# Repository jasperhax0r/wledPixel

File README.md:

# wledPixel
ESP32 or ESP8266 and MAX7219 dot matrix display management

## Notes
1. Currently it does take some time for the initial setup to become ready, usually under a minute before you can connect to its SSID
2. After resetting to factory defaults you may have to powercycle.
3. WOPR mode doesnt really have any current settings, only thing that can be configured is what workzone its in and brightness.

[The latest firmware version can be found in Releases](https://github.com/jasperhax0r/wledPixel/releases)

## Supported key features:
1. **Home Assistant client** [display sensor values]
2. **OpenWeatherMap client** [display: temperature (C/F), humidity, pressure, wind speed, weather icon]
3. **MQTT client** [each display zone support own topic]
4. Display controll through MQTT
5. **Wall NTP clock** [NTP sync clock]
6. **WOPR Blinking Lights**
7. **Manual input**
8. Full controll through **web UI**
9. Home Assistant MQTT discovery [When MQTT settings specified, device will be automatically send discovery message to HA]
10. Control display as light in Home Assistant [MQTT setup required]
11. Initial setup through wifi AP and web UI
12. Support 3 independent display zones
13. Support up to 12 display segments at the same time [configured in web UI]
14. Included 3 different fonts
15. Plus symbols font

##### Ingredients:
1. Dot matrix display MAX7219, something like this: https://aliexpress.com/item/32618155357.html
2. ESP32 or WeMos D1 Mini (ESP8266), something like this: https://aliexpress.com/item/32651747570.html

## Web UI - Settings

##### Firmware compiled with next parameters:
**ESP32**
NOTE: I had problems with some ESP32 modules and couldnt get them to consistantly work or boot at all.
```
// Display pinout
#define DATA_PIN  23         // ESP32 GPIO23
#define CS_PIN    5          // ESP32 GPIO5
#define CLK_PIN   18         // ESP32 GPIO18

// Ds18b20 pinout
const int oneWireBus = 4;    // ESP32 GPIO04
```

**ESP8266**
```
// Display pinout
#define DATA_PIN  D7         // WeMos D1 mini or ESP8266 -> GPIO13
#define CS_PIN    D6         // WeMos D1 mini or ESP8266 -> GPIO12
#define CLK_PIN   D5         // WeMos D1 mini or ESP8266 -> GPIO14

// Ds18b20 pinout
const int oneWireBus = D4;   // WeMos D1 mini or ESP8266 -> GPIO02
```

## Wiring

Note: when I was removing the pins so that i could solder the modules together I ran into constant problems with the pads ripping off the matrix modules. most of the time the fix was easy as the 5v, ground, CS and CLK pins are all wired in parallel. however for the DIN that required soldering a jumper wire from the DIN pin on the header to one of the pins on the MAX7219 chip. not too hard but just wanted to note this,

Also as a work in progress I have made a full [12 module single board](https://github.com/jasperhax0r/wledPixel/FullSizePCB/) in KiCad for a more simpler install. However currently it is cost prohibitive in low quantities.

## First boot:
> - Device will boot in wifi access point mode and write the wifi name and password on the display.
> - AP wifi name: **wledPixel-[short MAC address]**
> - AP wifi password: **12345678**
> - Connect to this AP and configure your wifi settings (connect to your wifi network)
> - When the device connects to the WIFI network, the device's IP address will be displayed on the zone0
> - Open the browser and go to the device IP address

## API
```
/api/temperature      - get measured temperature from connected ds18b20 sensor
```

## Icons in Wled symbol font:

```
1 - "X"
2 - "stop"
3 - "rain"
4 - "ip:"
8 - "full light segment"
A - "calendar"
B - "windows"
C - "clouds"
D - "door"
E - "female"
F - "snowflake"
G - "key"
H - "male"
I - "alarm"
J - "clock"
K - "garbage"
L - "info"
M - "moon"
N - "message"
O - "reminder"
P - "wifi"
R - "huge rain"
S - "sun"
T - "thunderstorm"
c - "cloud"
f - "fog"
m - "cloud and moon"
r - "rain"
s - "sun and cloud"
° - "degree symbol"
```

## MQTT topics:
* `devicePrefix/zoneN/workMode`         - zone work mode
* `devicePrefix/zoneN/scrolleffectIn`   - scroll effect IN
* `devicePrefix/zoneN/scrolleffectOut`  - scroll effect Out
* `devicePrefix/zoneN/scrollspeed`      - scroll speed
* `devicePrefix/zoneN/scrollpause`      - scroll pause
* `devicePrefix/zoneN/scrollalign`      - scroll alignment
* `devicePrefix/zoneN/charspacing`      - character spacing
* `devicePrefix/intensity`              - brightness
* `devicePrefix/zoneN/workMode`         - zone work mode
* `devicePrefix/power`                  - display power control, support on / off values

where **devicePrefix** = wledPixel-A071
**zoneN** = zone number (e.g. Zone0)

#### Supported workMode:
workMode supported values:
* `mqttClient`    - MQTT client
* `manualInput`   - Manual static text inputed in UI
* `wallClock`     - NTP sync clock
* `owmWeather`    - Open Weather Map client
* `haClient`      - Home Assistant client
* `wopr`          - WOPR Blinking Lights Mode

## Wall clock
Wall clock mode support next following display options:
* `HH:MM`       - Hours : Minutes [21:43]
* `HH:MM:SS`    - Hours : Minutes : Seconds [21:43:54]
* `HH`          - Hours [21]
* `MM`          - Minutes [43]
* `dd.mm.yyyy`  - Day.Month.Year [21.06.2022]
* `dd.mm`       - Day.Month [21.06]
* `dd.mm aa`    - Day.Month weekday name (e.g., Sun) [21.06 Tue] *in Cyrillic font weekday name will be in Cyrillic
* `aa`          - Weekday name (e.g. Sun) *in Cyrillic font weekday name will be in Cyrillic

## Scroll effect list
Default effects:
* `PA_RANDOM`
* `PA_PRINT`
* `PA_SCAN_HORIZ`
* `PA_SCROLL_LEFT`
* `PA_WIPE`
* `PA_SCAN_VERTX`
* `PA_SCROLL_UP_LEFT`
* `PA_SCROLL_UP`
* `PA_FADE`
* `PA_OPENING_CURSOR`
* `PA_GROW_UP`
* `PA_SCROLL_UP_RIGHT`
* `PA_BLINDS`
* `PA_CLOSING`
* `PA_GROW_DOWN`
* `PA_SCAN_VERT`
* `PA_SCROLL_DOWN_LEFT`
* `PA_WIPE_CURSOR`
* `PA_SCAN_HORIZX`
* `PA_DISSOLVE`
* `PA_MESH`
* `PA_OPENING`
* `PA_CLOSING_CURSOR`
* `PA_SCROLL_DOWN_RIGHT`
* `PA_SCROLL_RIGHT`
* `PA_SLICE`
* `PA_SCROLL_DOWN`

## Home Assistant automation example:
Send sensor value each time when a value has been changed
```
---
- alias: Outside temp change - send new temp to wled panel mqtt
  initial_state: 'on'
  trigger:
    platform: state
    entity_id: sensor.outside_thp_sensor_3
  action:
    - service: mqtt.publish
      data:
        topic: wledPixel-A071/zone0/text
        payload_template: "{{ states('sensor.outside_thp_sensor_3') }} C"
```
Change **wledPixel-A071** to device name with your prefix

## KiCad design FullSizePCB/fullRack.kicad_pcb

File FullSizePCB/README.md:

# Full Size PCB Schematics and Gerber Files

## About the PCB
This PCB is basically 12 single modules connected together as one, using only through hole components to make it easier to hand solder.

*Note: while designed looking up the costs for the parts it is cheaper by far to just connect several premade modules together*

## BOM
* 12 x MAX7219CNG+
* 12 x 10k Resistors
* 12 x 0.1uF Ceramic Capacitors
* 12 x 10uF/25v Ceramic Capacitors
* 12 x TA08-81GWA 8x8 Matrix LED's
* 1 x 5pin Header

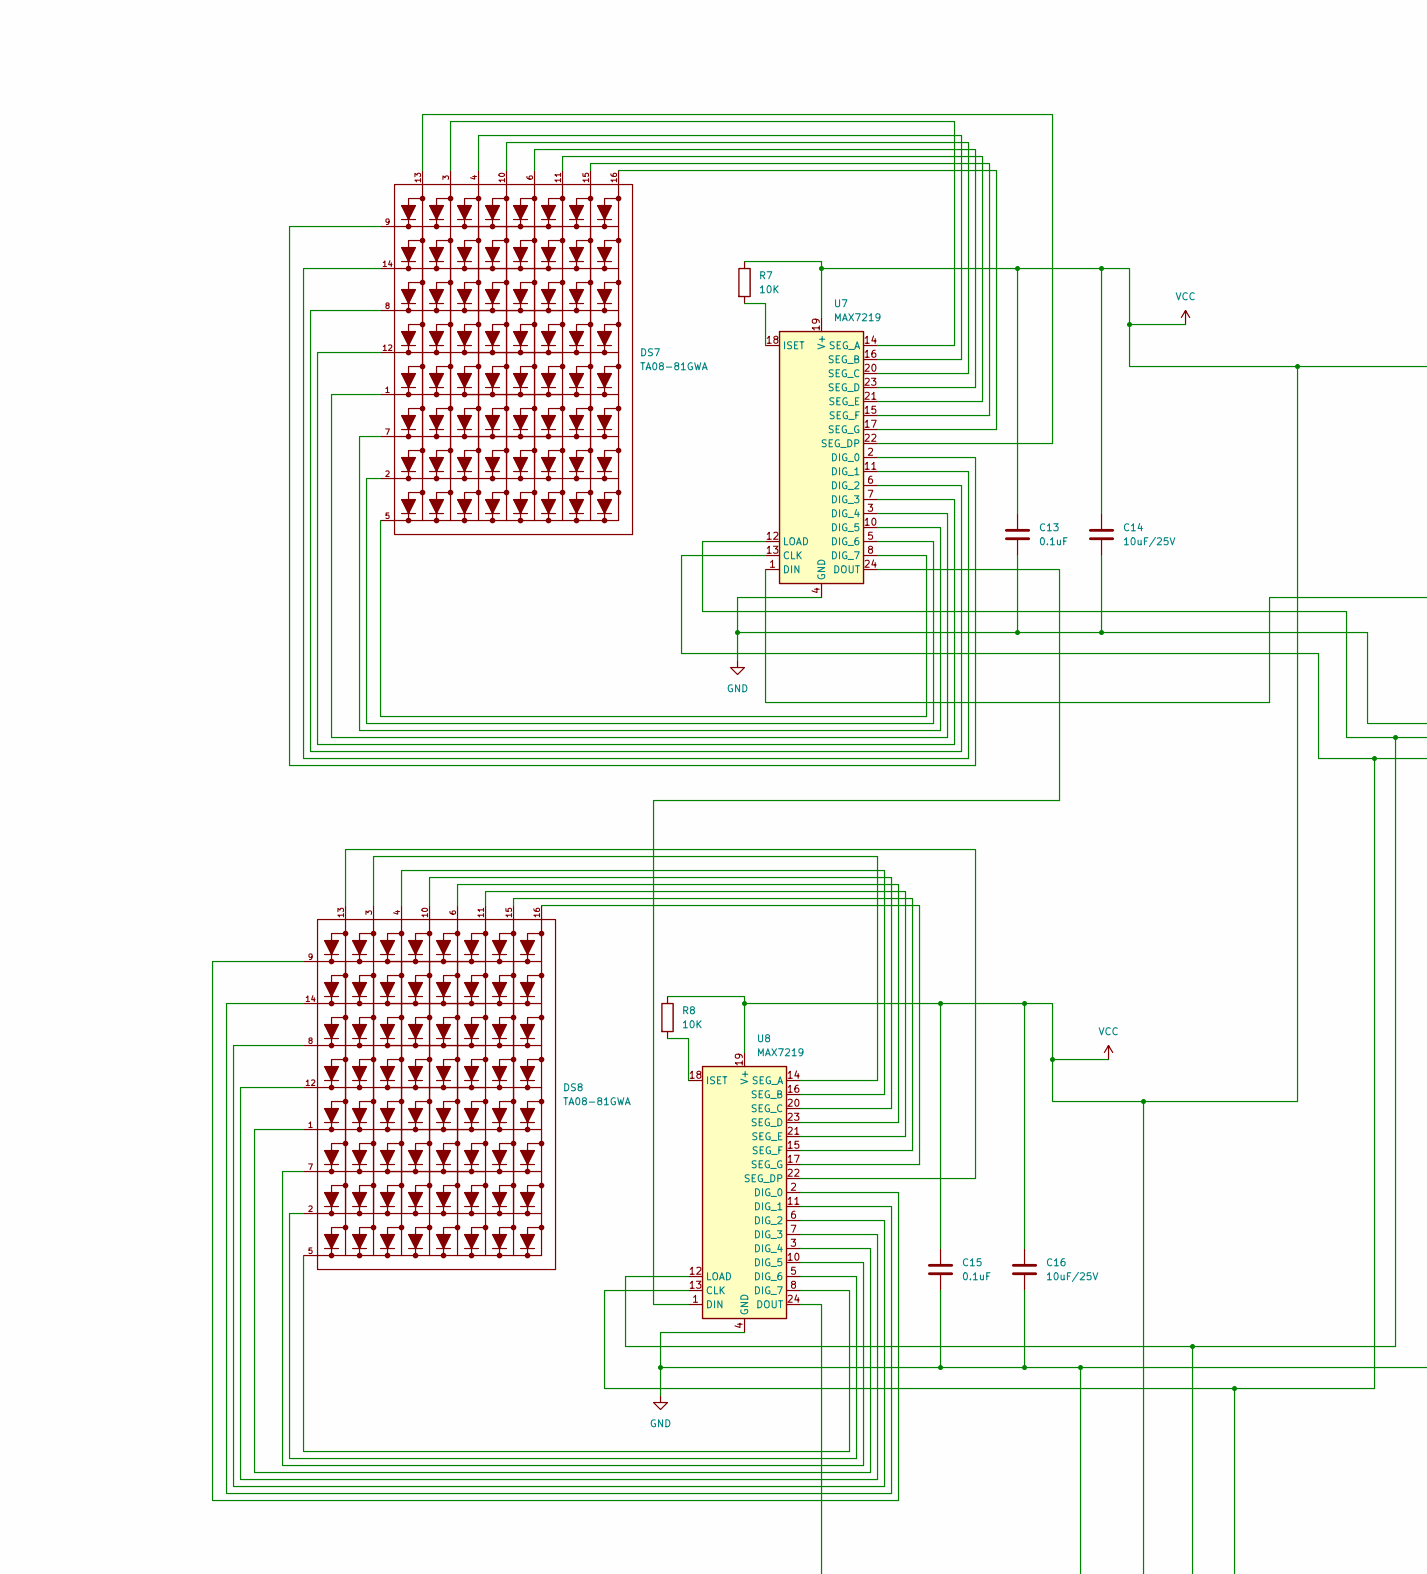
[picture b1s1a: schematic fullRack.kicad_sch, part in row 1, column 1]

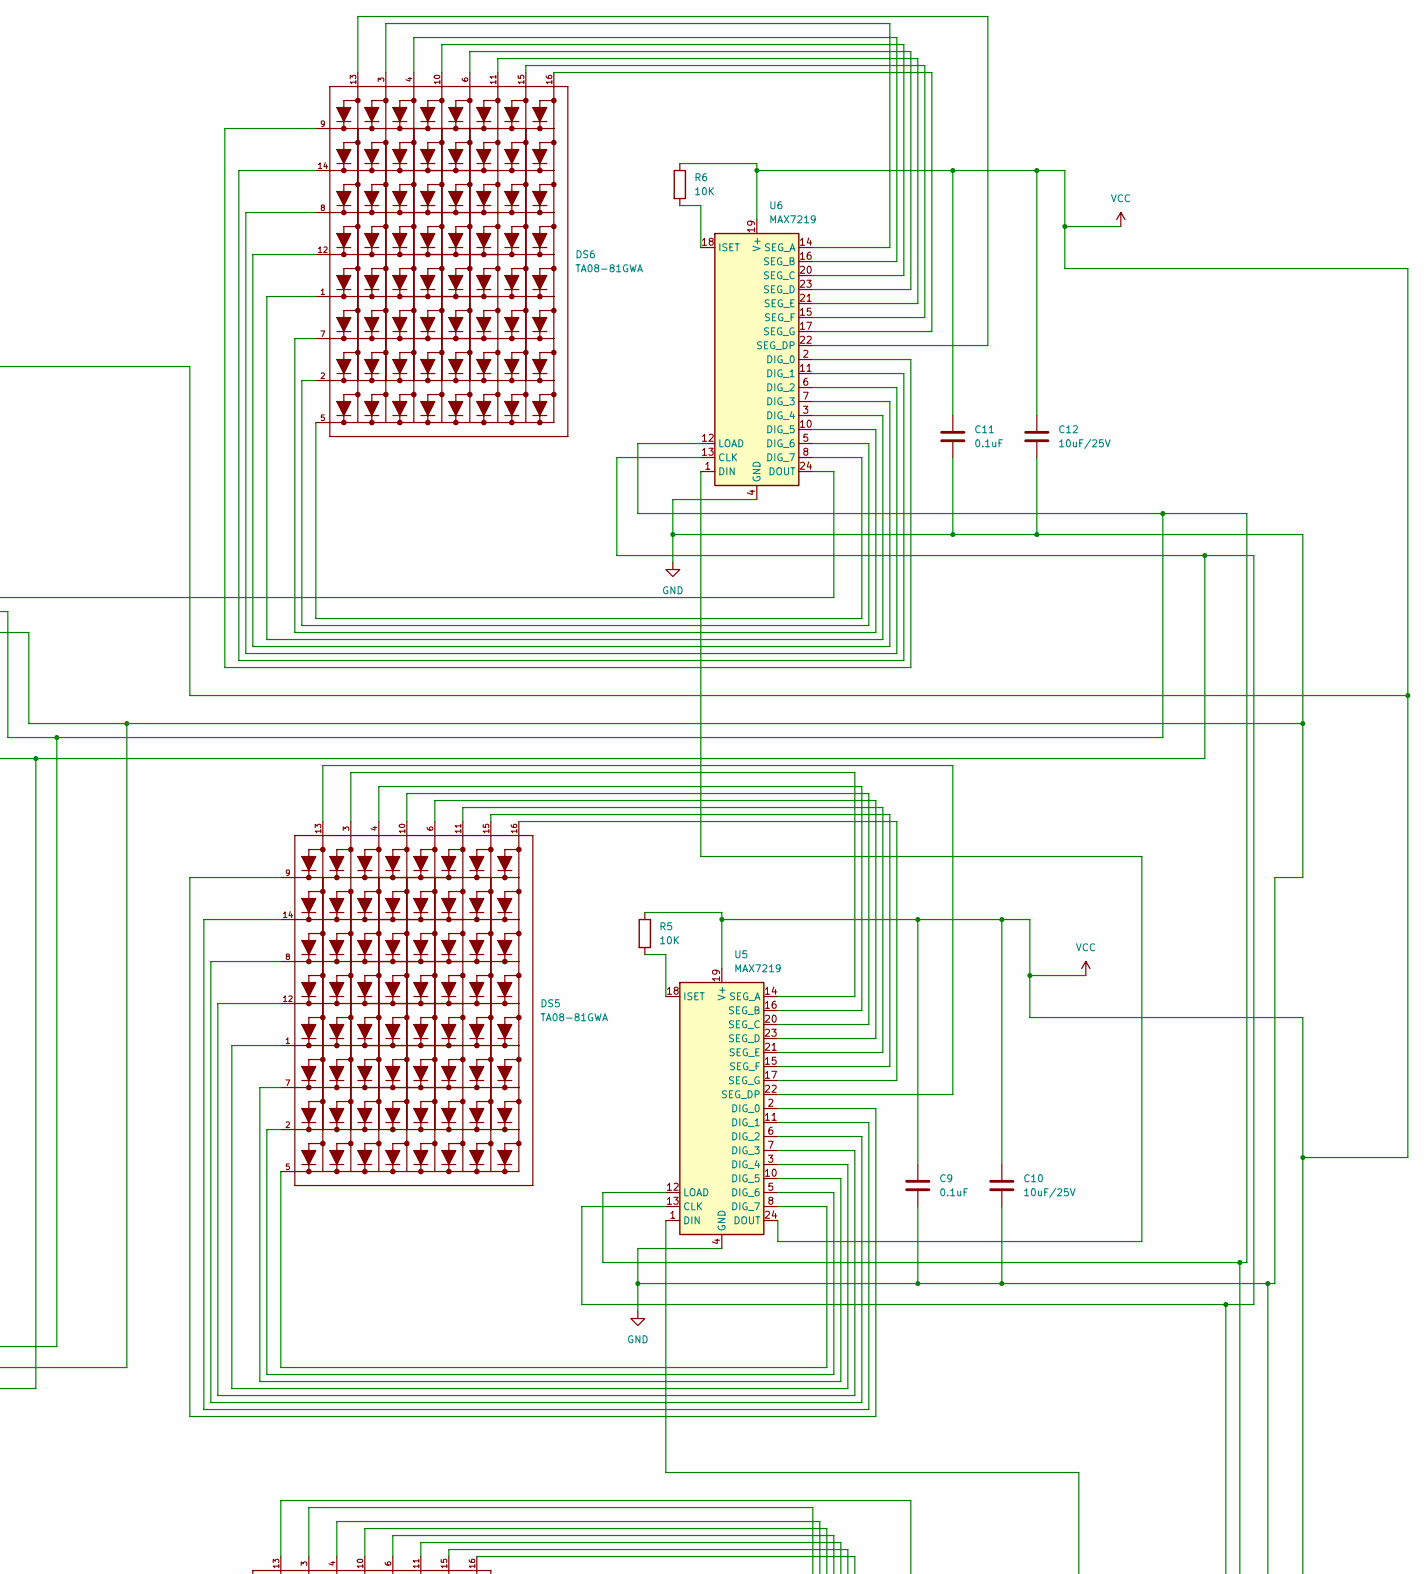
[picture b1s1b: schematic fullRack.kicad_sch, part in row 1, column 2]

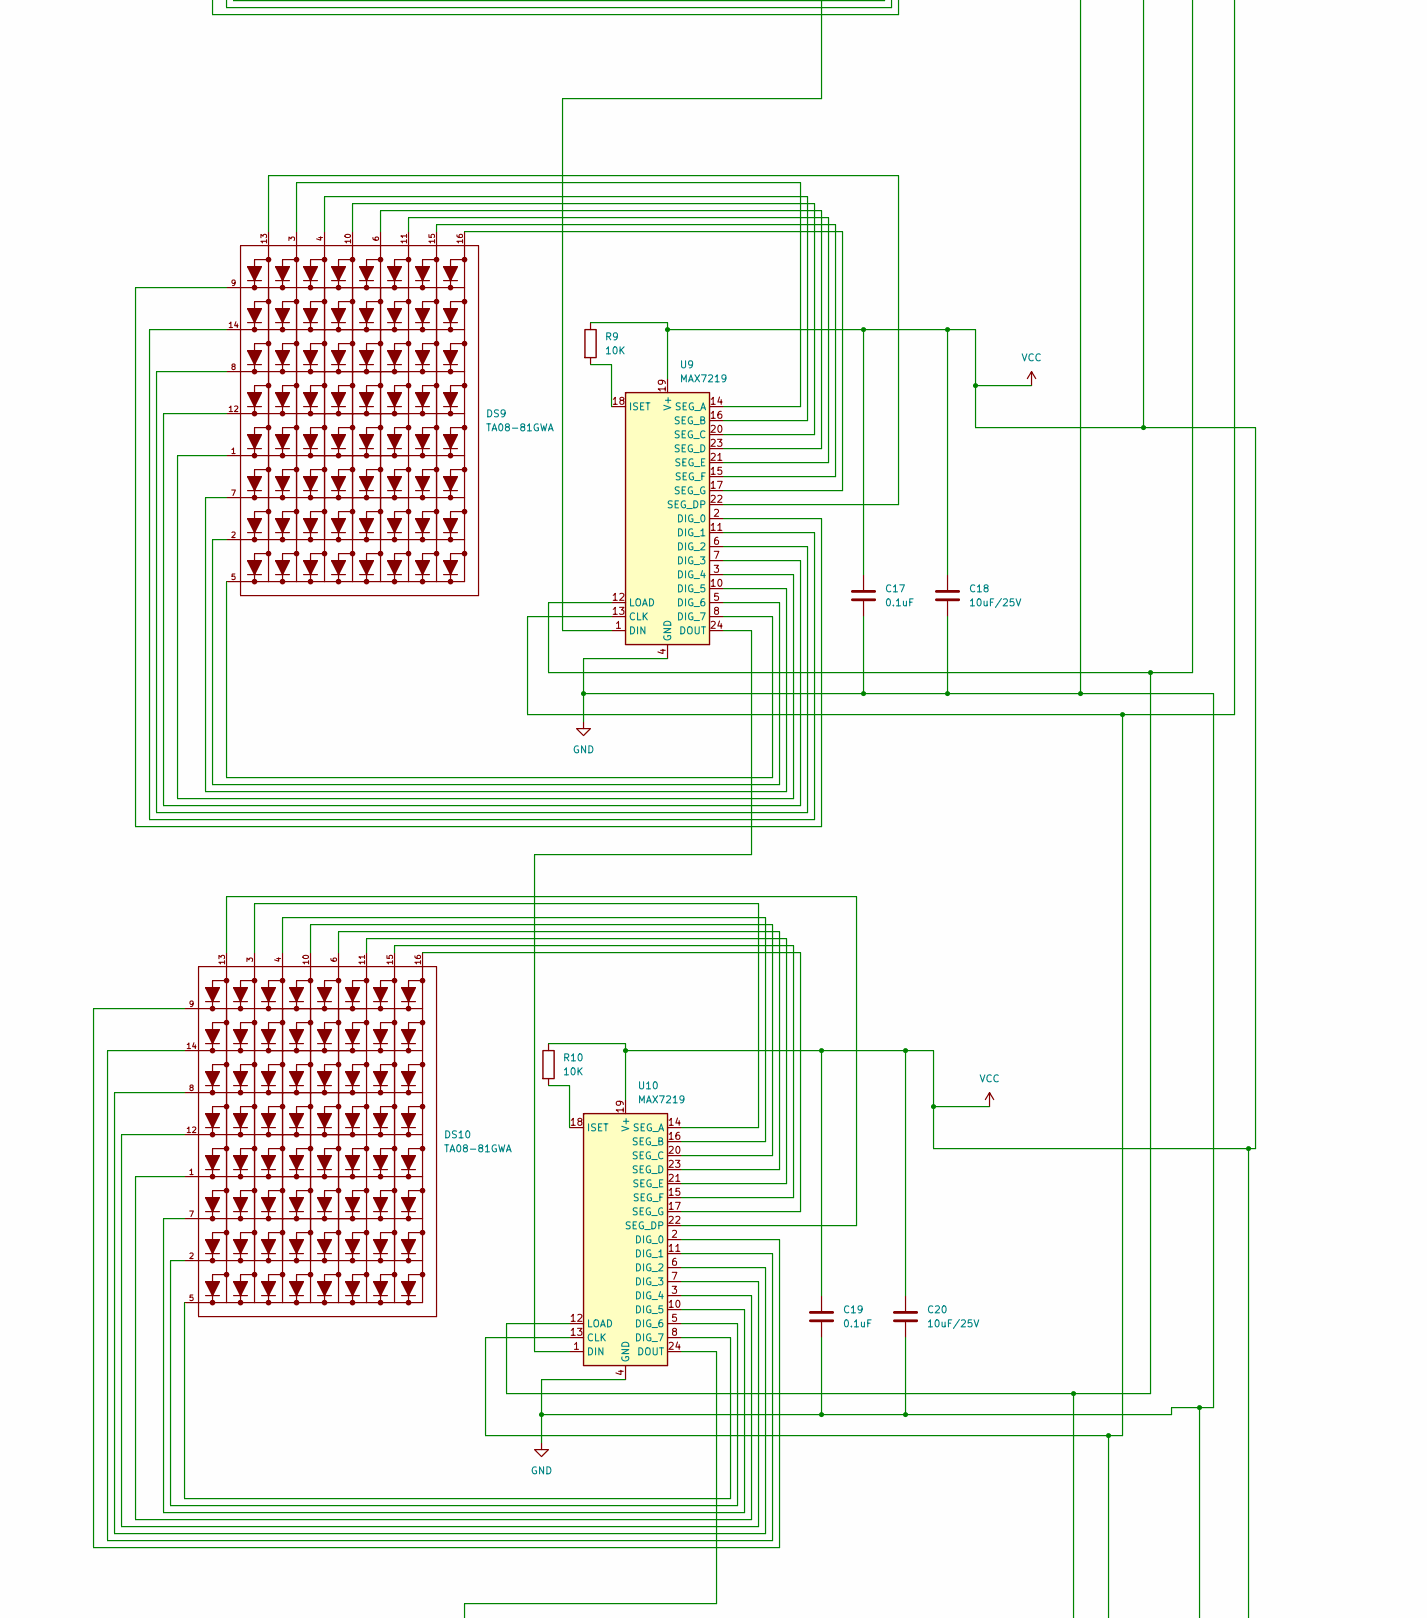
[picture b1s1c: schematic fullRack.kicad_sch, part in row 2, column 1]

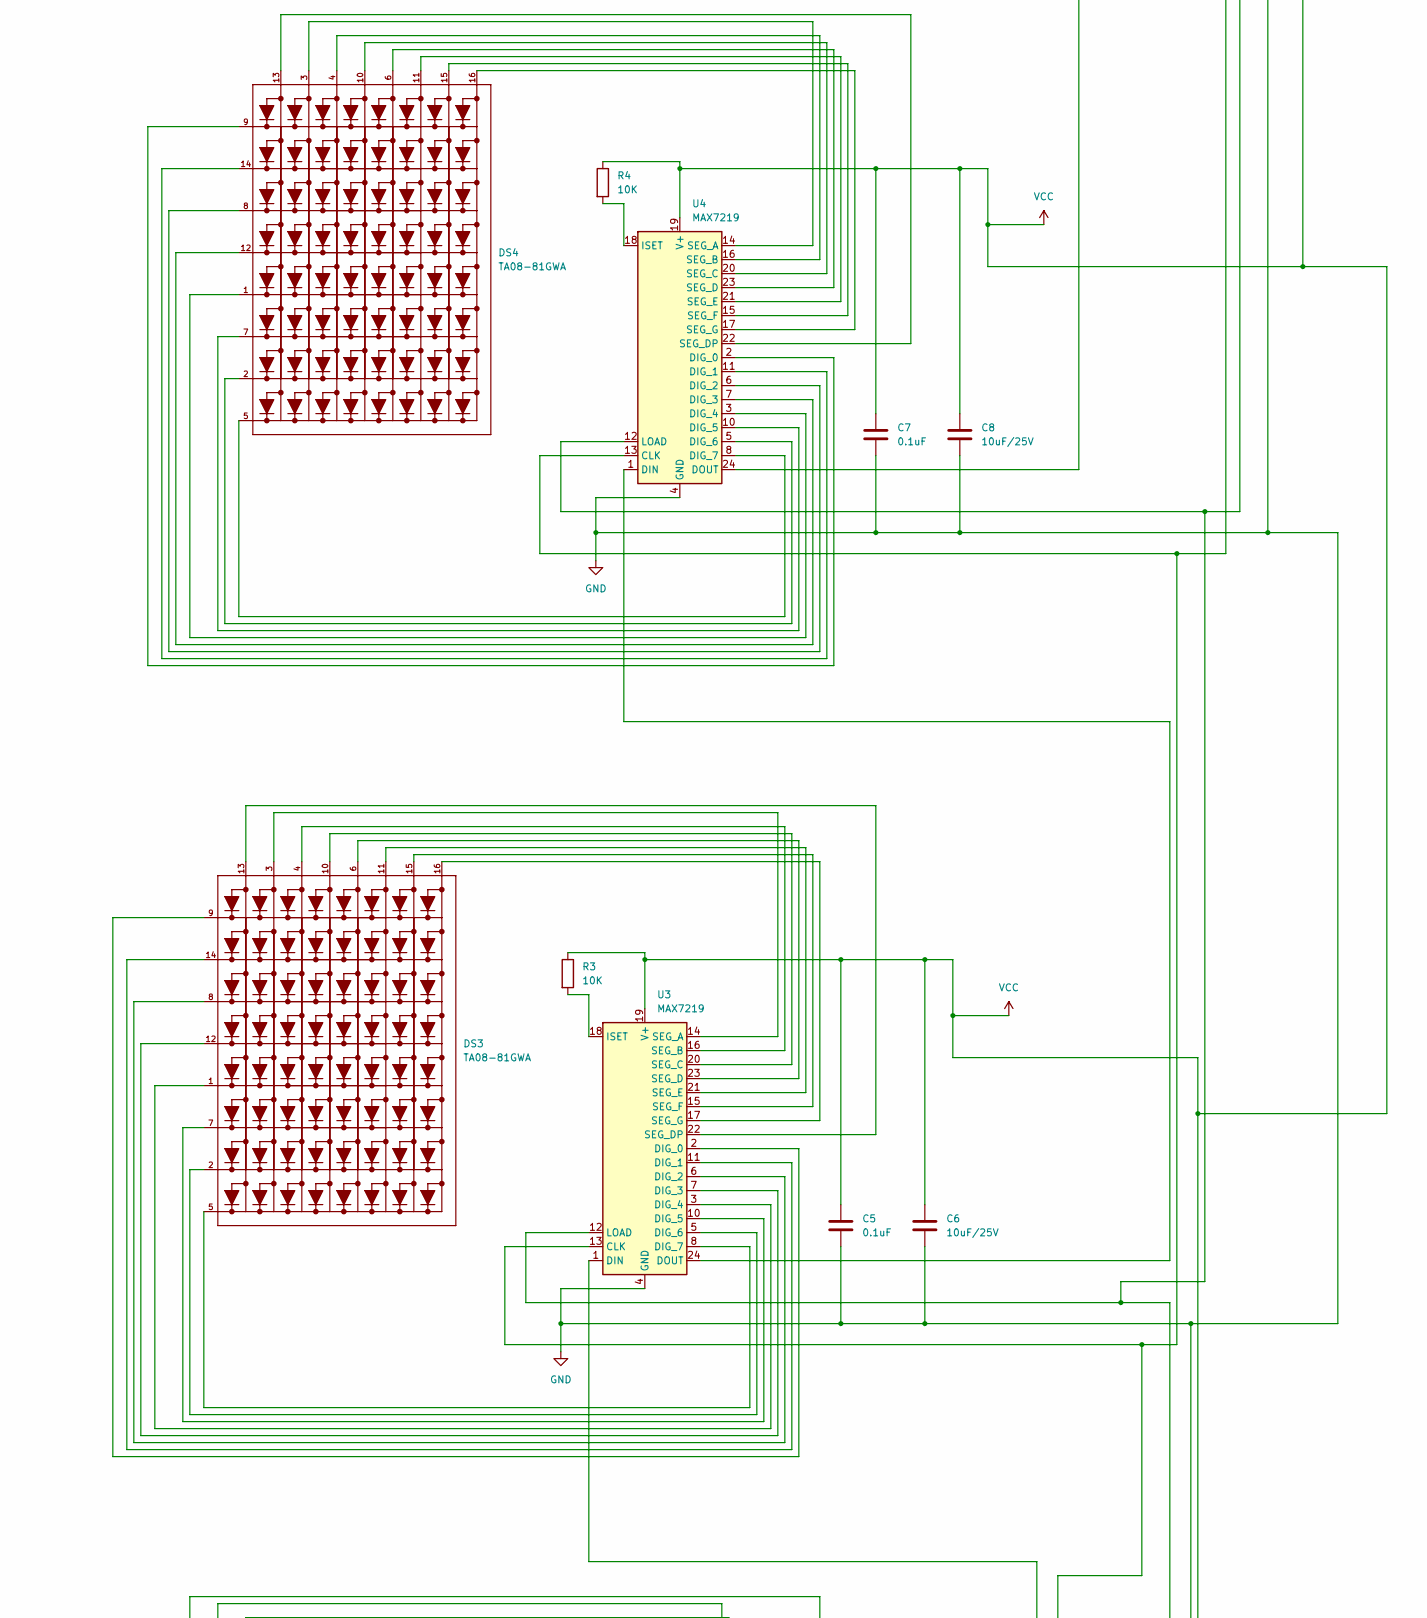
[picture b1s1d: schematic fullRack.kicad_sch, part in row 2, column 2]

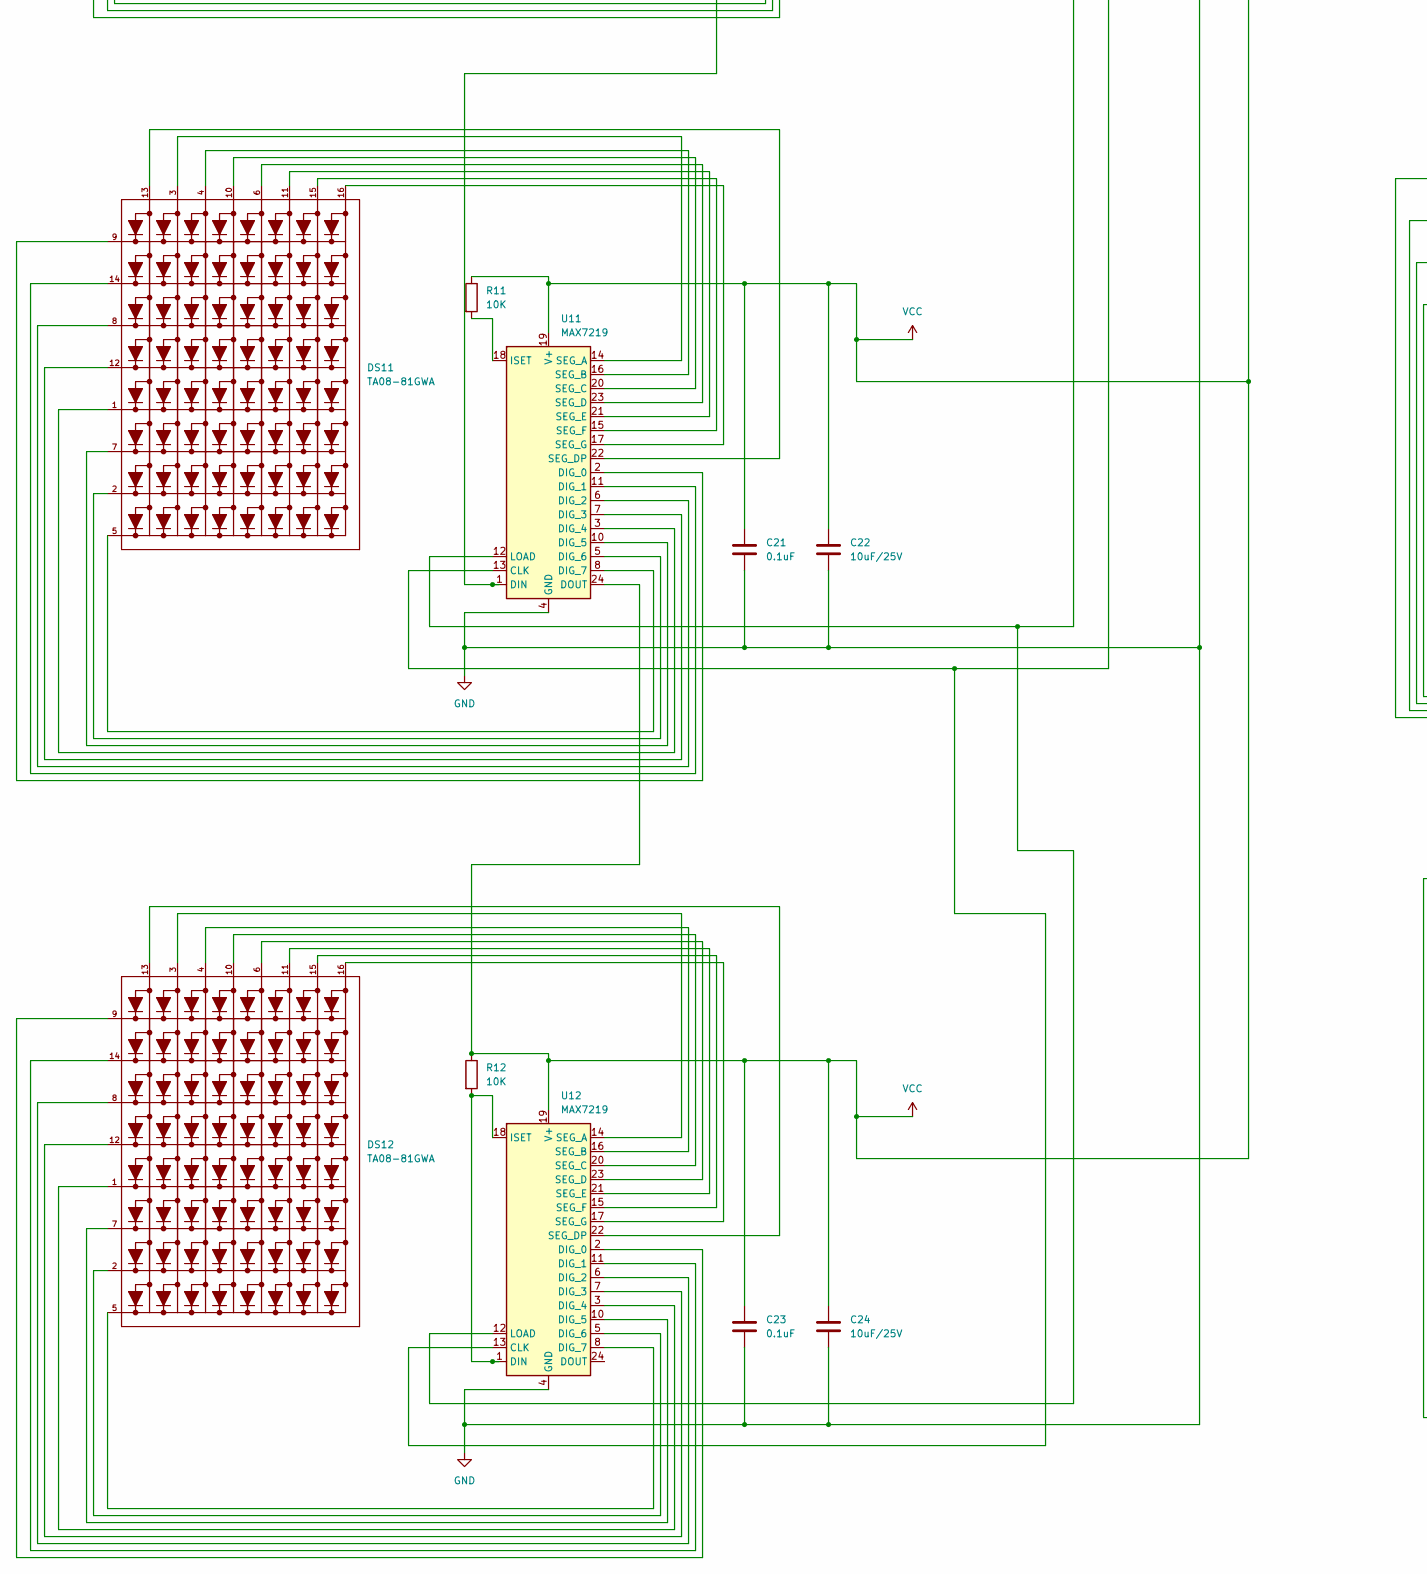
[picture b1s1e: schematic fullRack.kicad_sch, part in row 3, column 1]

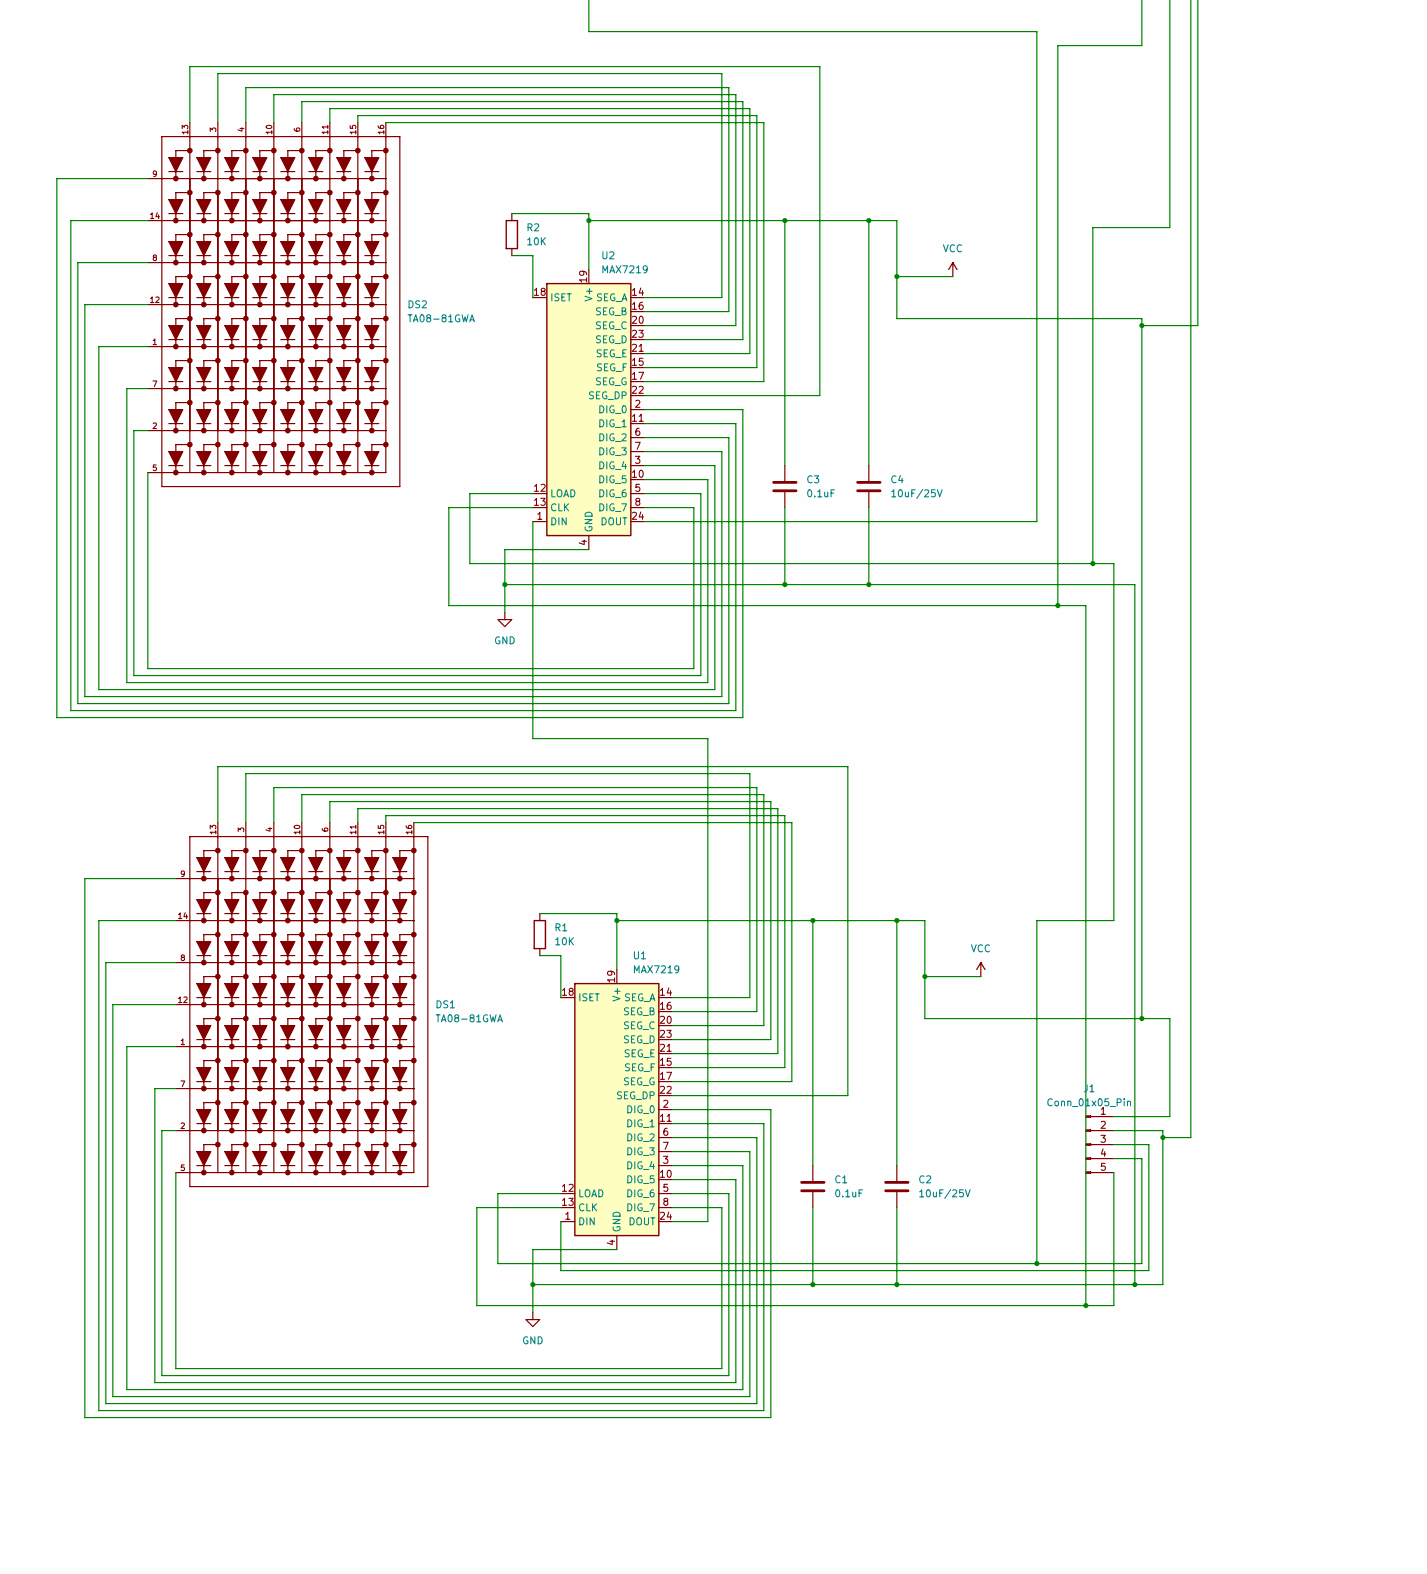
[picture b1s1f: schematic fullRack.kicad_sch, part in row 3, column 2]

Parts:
C1, C3, C5, C7, C9, C11, C13, C15, C17, C19, C21, C23: 0.1uF; C_Disc_D3.8mm_W2.6mm_P2.50mm
C2, C4, C6, C8, C10, C12, C14, C16, C18, C20, C22, C24: 10uF/25V; C_Disc_D3.8mm_W2.6mm_P2.50mm
DS1, DS2, DS3, DS4, DS5, DS6, DS7, DS8, DS9, DS10, DS11, DS12: TA08-81GWA; DISPLAY_TA08-81GWA; PARTREV V.11A
J1: Conn_01x05_Pin; PinHeader_1x05_P2.54mm_Horizontal
R1, R2, R3, R4, R5, R6, R7, R8, R9, R10, R11, R12: 10K; R_Axial_DIN0204_L3.6mm_D1.6mm_P7.62mm_Horizontal
U1, U2, U3, U4, U5, U6, U7, U8, U9, U10, U11, U12: MAX7219; DIP-24_W7.62mm

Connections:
GND: C1.2, C2.2, C3.2, C4.2, C5.2, C6.2, C7.2, C8.2, C9.2, C10.2, C11.2, C12.2, C13.2, C14.2, C15.2, C16.2, C17.2, C18.2, C19.2, C20.2, C21.2, C22.2, C23.2, C24.2, J1.2, U1.4 (GND), U1.9 (GND), U2.4 (GND), U2.9 (GND), U3.4 (GND), U3.9 (GND), U4.4 (GND), U4.9 (GND), U5.4 (GND), U5.9 (GND), U6.4 (GND), U6.9 (GND), U7.4 (GND), U7.9 (GND), U8.4 (GND), U8.9 (GND), U9.4 (GND), U9.9 (GND), U10.4 (GND), U10.9 (GND), U11.4 (GND), U11.9 (GND), U12.4 (GND), U12.9 (GND)
unnamed: J1.3, U1.1 (DIN)
unnamed: J1.4, U1.12 (LOAD), U2.12 (LOAD), U3.12 (LOAD), U4.12 (LOAD), U5.12 (LOAD), U6.12 (LOAD), U7.12 (LOAD), U8.12 (LOAD), U9.12 (LOAD), U10.12 (LOAD), U11.12 (LOAD), U12.12 (LOAD)
unnamed: J1.5, U1.13 (CLK), U2.13 (CLK), U3.13 (CLK), U4.13 (CLK), U5.13 (CLK), U6.13 (CLK), U7.13 (CLK), U8.13 (CLK), U9.13 (CLK), U10.13 (CLK), U11.13 (CLK), U12.13 (CLK)
unnamed: DS1.9, U1.2 (DIG_0)
unnamed: DS1.14, U1.11 (DIG_1)
unnamed: DS1.8, U1.6 (DIG_2)
unnamed: DS1.12, U1.7 (DIG_3)
unnamed: DS1.1, U1.3 (DIG_4)
unnamed: DS1.7, U1.10 (DIG_5)
unnamed: DS1.2, U1.5 (DIG_6)
unnamed: DS1.5, U1.8 (DIG_7)
unnamed: U1.24 (DOUT), U2.1 (DIN)
unnamed: R1.2, U1.18 (ISET)
unnamed: DS1.3, U1.14 (SEG_A)
unnamed: DS1.4, U1.16 (SEG_B)
unnamed: DS1.10, U1.20 (SEG_C)
unnamed: DS1.6, U1.23 (SEG_D)
unnamed: DS1.13, U1.22 (SEG_DP)
unnamed: DS1.11, U1.21 (SEG_E)
unnamed: DS1.15, U1.15 (SEG_F)
unnamed: DS1.16, U1.17 (SEG_G)
unnamed: DS2.9, U2.2 (DIG_0)
unnamed: DS2.14, U2.11 (DIG_1)
unnamed: DS2.8, U2.6 (DIG_2)
unnamed: DS2.12, U2.7 (DIG_3)
unnamed: DS2.1, U2.3 (DIG_4)
unnamed: DS2.7, U2.10 (DIG_5)
unnamed: DS2.2, U2.5 (DIG_6)
unnamed: DS2.5, U2.8 (DIG_7)
unnamed: U2.24 (DOUT), U3.1 (DIN)
unnamed: R2.2, U2.18 (ISET)
unnamed: DS2.3, U2.14 (SEG_A)
unnamed: DS2.4, U2.16 (SEG_B)
unnamed: DS2.10, U2.20 (SEG_C)
unnamed: DS2.6, U2.23 (SEG_D)
unnamed: DS2.13, U2.22 (SEG_DP)
unnamed: DS2.11, U2.21 (SEG_E)
unnamed: DS2.15, U2.15 (SEG_F)
unnamed: DS2.16, U2.17 (SEG_G)
unnamed: DS3.9, U3.2 (DIG_0)
unnamed: DS3.14, U3.11 (DIG_1)
unnamed: DS3.8, U3.6 (DIG_2)
unnamed: DS3.12, U3.7 (DIG_3)
unnamed: DS3.1, U3.3 (DIG_4)
unnamed: DS3.7, U3.10 (DIG_5)
unnamed: DS3.2, U3.5 (DIG_6)
unnamed: DS3.5, U3.8 (DIG_7)
unnamed: U3.24 (DOUT), U4.1 (DIN)
unnamed: R3.2, U3.18 (ISET)
unnamed: DS3.3, U3.14 (SEG_A)
unnamed: DS3.4, U3.16 (SEG_B)
unnamed: DS3.10, U3.20 (SEG_C)
unnamed: DS3.6, U3.23 (SEG_D)
unnamed: DS3.13, U3.22 (SEG_DP)
unnamed: DS3.11, U3.21 (SEG_E)
unnamed: DS3.15, U3.15 (SEG_F)
unnamed: DS3.16, U3.17 (SEG_G)
unnamed: DS4.9, U4.2 (DIG_0)
unnamed: DS4.14, U4.11 (DIG_1)
unnamed: DS4.8, U4.6 (DIG_2)
unnamed: DS4.12, U4.7 (DIG_3)
unnamed: DS4.1, U4.3 (DIG_4)
unnamed: DS4.7, U4.10 (DIG_5)
unnamed: DS4.2, U4.5 (DIG_6)
unnamed: DS4.5, U4.8 (DIG_7)
unnamed: U4.24 (DOUT), U5.1 (DIN)
unnamed: R4.2, U4.18 (ISET)
unnamed: DS4.3, U4.14 (SEG_A)
unnamed: DS4.4, U4.16 (SEG_B)
unnamed: DS4.10, U4.20 (SEG_C)
unnamed: DS4.6, U4.23 (SEG_D)
unnamed: DS4.13, U4.22 (SEG_DP)
unnamed: DS4.11, U4.21 (SEG_E)
unnamed: DS4.15, U4.15 (SEG_F)
unnamed: DS4.16, U4.17 (SEG_G)
unnamed: DS5.9, U5.2 (DIG_0)
unnamed: DS5.14, U5.11 (DIG_1)
unnamed: DS5.8, U5.6 (DIG_2)
unnamed: DS5.12, U5.7 (DIG_3)
unnamed: DS5.1, U5.3 (DIG_4)
unnamed: DS5.7, U5.10 (DIG_5)
unnamed: DS5.2, U5.5 (DIG_6)
unnamed: DS5.5, U5.8 (DIG_7)
unnamed: U5.24 (DOUT), U6.1 (DIN)
unnamed: R5.2, U5.18 (ISET)
unnamed: DS5.3, U5.14 (SEG_A)
unnamed: DS5.4, U5.16 (SEG_B)
unnamed: DS5.10, U5.20 (SEG_C)
unnamed: DS5.6, U5.23 (SEG_D)
unnamed: DS5.13, U5.22 (SEG_DP)
unnamed: DS5.11, U5.21 (SEG_E)
unnamed: DS5.15, U5.15 (SEG_F)
unnamed: DS5.16, U5.17 (SEG_G)
unnamed: DS6.9, U6.2 (DIG_0)
unnamed: DS6.14, U6.11 (DIG_1)
unnamed: DS6.8, U6.6 (DIG_2)
unnamed: DS6.12, U6.7 (DIG_3)
unnamed: DS6.1, U6.3 (DIG_4)
unnamed: DS6.7, U6.10 (DIG_5)
unnamed: DS6.2, U6.5 (DIG_6)
unnamed: DS6.5, U6.8 (DIG_7)
unnamed: U6.24 (DOUT), U7.1 (DIN)
unnamed: R6.2, U6.18 (ISET)
unnamed: DS6.3, U6.14 (SEG_A)
unnamed: DS6.4, U6.16 (SEG_B)
unnamed: DS6.10, U6.20 (SEG_C)
unnamed: DS6.6, U6.23 (SEG_D)
unnamed: DS6.13, U6.22 (SEG_DP)
unnamed: DS6.11, U6.21 (SEG_E)
unnamed: DS6.15, U6.15 (SEG_F)
unnamed: DS6.16, U6.17 (SEG_G)
unnamed: DS7.9, U7.2 (DIG_0)
unnamed: DS7.14, U7.11 (DIG_1)
unnamed: DS7.8, U7.6 (DIG_2)
unnamed: DS7.12, U7.7 (DIG_3)
unnamed: DS7.1, U7.3 (DIG_4)
unnamed: DS7.7, U7.10 (DIG_5)
unnamed: DS7.2, U7.5 (DIG_6)
unnamed: DS7.5, U7.8 (DIG_7)
unnamed: U7.24 (DOUT), U8.1 (DIN)
unnamed: R7.2, U7.18 (ISET)
unnamed: DS7.3, U7.14 (SEG_A)
unnamed: DS7.4, U7.16 (SEG_B)
unnamed: DS7.10, U7.20 (SEG_C)
unnamed: DS7.6, U7.23 (SEG_D)
unnamed: DS7.13, U7.22 (SEG_DP)
unnamed: DS7.11, U7.21 (SEG_E)
unnamed: DS7.15, U7.15 (SEG_F)
unnamed: DS7.16, U7.17 (SEG_G)
unnamed: DS8.9, U8.2 (DIG_0)
unnamed: DS8.14, U8.11 (DIG_1)
unnamed: DS8.8, U8.6 (DIG_2)
unnamed: DS8.12, U8.7 (DIG_3)
unnamed: DS8.1, U8.3 (DIG_4)
unnamed: DS8.7, U8.10 (DIG_5)
unnamed: DS8.2, U8.5 (DIG_6)
unnamed: DS8.5, U8.8 (DIG_7)
unnamed: U8.24 (DOUT), U9.1 (DIN)
unnamed: R8.2, U8.18 (ISET)
unnamed: DS8.3, U8.14 (SEG_A)
unnamed: DS8.4, U8.16 (SEG_B)
unnamed: DS8.10, U8.20 (SEG_C)
unnamed: DS8.6, U8.23 (SEG_D)
unnamed: DS8.13, U8.22 (SEG_DP)
unnamed: DS8.11, U8.21 (SEG_E)
unnamed: DS8.15, U8.15 (SEG_F)
unnamed: DS8.16, U8.17 (SEG_G)
unnamed: DS9.9, U9.2 (DIG_0)
unnamed: DS9.14, U9.11 (DIG_1)
unnamed: DS9.8, U9.6 (DIG_2)
unnamed: DS9.12, U9.7 (DIG_3)
unnamed: DS9.1, U9.3 (DIG_4)
unnamed: DS9.7, U9.10 (DIG_5)
unnamed: DS9.2, U9.5 (DIG_6)
unnamed: DS9.5, U9.8 (DIG_7)
unnamed: R9.2, U9.18 (ISET)
unnamed: DS9.3, U9.14 (SEG_A)
unnamed: DS9.4, U9.16 (SEG_B)
unnamed: DS9.10, U9.20 (SEG_C)
unnamed: DS9.6, U9.23 (SEG_D)
unnamed: DS9.13, U9.22 (SEG_DP)
unnamed: DS9.11, U9.21 (SEG_E)
unnamed: DS9.15, U9.15 (SEG_F)
unnamed: DS9.16, U9.17 (SEG_G)
unnamed: DS10.9, U10.2 (DIG_0)
unnamed: DS10.14, U10.11 (DIG_1)
unnamed: DS10.8, U10.6 (DIG_2)
unnamed: DS10.12, U10.7 (DIG_3)
unnamed: DS10.1, U10.3 (DIG_4)
unnamed: DS10.7, U10.10 (DIG_5)
unnamed: DS10.2, U10.5 (DIG_6)
unnamed: DS10.5, U10.8 (DIG_7)
unnamed: U9.24 (DOUT), U10.1 (DIN)
unnamed: U10.24 (DOUT), U11.1 (DIN)
unnamed: R10.2, U10.18 (ISET)
unnamed: DS10.3, U10.14 (SEG_A)
unnamed: DS10.4, U10.16 (SEG_B)
unnamed: DS10.10, U10.20 (SEG_C)
unnamed: DS10.6, U10.23 (SEG_D)
unnamed: DS10.13, U10.22 (SEG_DP)
unnamed: DS10.11, U10.21 (SEG_E)
unnamed: DS10.15, U10.15 (SEG_F)
unnamed: DS10.16, U10.17 (SEG_G)
unnamed: DS11.9, U11.2 (DIG_0)
unnamed: DS11.14, U11.11 (DIG_1)
unnamed: DS11.8, U11.6 (DIG_2)
unnamed: DS11.12, U11.7 (DIG_3)
unnamed: DS11.1, U11.3 (DIG_4)
unnamed: DS11.7, U11.10 (DIG_5)
unnamed: DS11.2, U11.5 (DIG_6)
unnamed: DS11.5, U11.8 (DIG_7)
unnamed: R11.2, U11.18 (ISET)
unnamed: DS11.3, U11.14 (SEG_A)
unnamed: DS11.4, U11.16 (SEG_B)
unnamed: DS11.10, U11.20 (SEG_C)
unnamed: DS11.6, U11.23 (SEG_D)
unnamed: DS11.13, U11.22 (SEG_DP)
unnamed: DS11.11, U11.21 (SEG_E)
unnamed: DS11.15, U11.15 (SEG_F)
unnamed: DS11.16, U11.17 (SEG_G)
unnamed: DS12.9, U12.2 (DIG_0)
unnamed: DS12.14, U12.11 (DIG_1)
unnamed: DS12.8, U12.6 (DIG_2)
unnamed: DS12.12, U12.7 (DIG_3)
unnamed: DS12.1, U12.3 (DIG_4)
unnamed: DS12.7, U12.10 (DIG_5)
unnamed: DS12.2, U12.5 (DIG_6)
unnamed: DS12.5, U12.8 (DIG_7)
unnamed: R12.2, U12.1 (DIN), U12.18 (ISET)
unnamed: DS12.3, U12.14 (SEG_A)
unnamed: DS12.4, U12.16 (SEG_B)
unnamed: DS12.10, U12.20 (SEG_C)
unnamed: DS12.6, U12.23 (SEG_D)
unnamed: DS12.13, U12.22 (SEG_DP)
unnamed: DS12.11, U12.21 (SEG_E)
unnamed: DS12.15, U12.15 (SEG_F)
unnamed: DS12.16, U12.17 (SEG_G)
VCC: C1.1, C2.1, C3.1, C4.1, C5.1, C6.1, C7.1, C8.1, C9.1, C10.1, C11.1, C12.1, C13.1, C14.1, C15.1, C16.1, C17.1, C18.1, C19.1, C20.1, C21.1, C22.1, C23.1, C24.1, J1.1, R1.1, R2.1, R3.1, R4.1, R5.1, R6.1, R7.1, R8.1, R9.1, R10.1, R11.1, R12.1, U1.19 (V+), U2.19 (V+), U3.19 (V+), U4.19 (V+), U5.19 (V+), U6.19 (V+), U7.19 (V+), U8.19 (V+), U9.19 (V+), U10.19 (V+), U11.19 (V+), U11.24 (DOUT), U12.19 (V+)

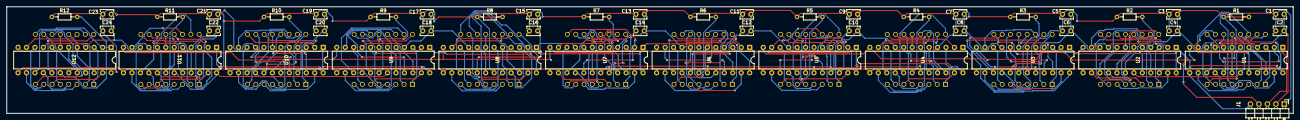
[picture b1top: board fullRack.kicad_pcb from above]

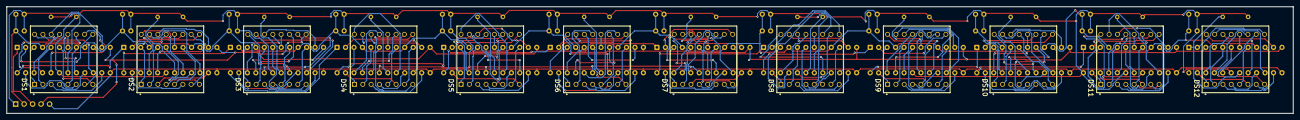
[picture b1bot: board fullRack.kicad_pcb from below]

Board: 2 copper layers, 386.1 x 32.0 mm, 61 parts (12 on the bottom side), 219 nets.

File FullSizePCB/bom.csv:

Designator,Footprint,Quantity,Value,LCSC Part #
"C1, C11, C13, C15, C17, C19, C21, C23, C3, C5, C7, C9",C_Disc_D3.8mm_W2.6mm_P2.50mm,12,0.1uF,
"C10, C12, C14, C16, C18, C2, C20, C22, C24, C4, C6, C8",C_Disc_D3.8mm_W2.6mm_P2.50mm,12,10uF/25V,
"DS1, DS10, DS11, DS12, DS2, DS3, DS4, DS5, DS6, DS7, DS8, DS9",DISPLAY_TA08-81GWA,12,TA08-81GWA,
J1,PinHeader_1x05_P2.54mm_Horizontal,1,Conn_01x05_Pin,
"R1, R10, R11, R12, R2, R3, R4, R5, R6, R7, R8, R9",R_Axial_DIN0204_L3.6mm_D1.6mm_P7.62mm_Horizontal,12,10K,
"U1, U10, U11, U12, U2, U3, U4, U5, U6, U7, U8, U9",DIP-24_W7.62mm,12,MAX7219,

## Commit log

2026-01-01 Added WOPR visual option
2026-01-02 Update README.md with WOPR image
2026-01-06 fixed the connection points between parts.
2026-01-15 Update README.md
    added some notes after building a few of these for some of the problems i ran into
2026-01-16 updated wopr function
    updated wopr function so it no longer flashes at full brightness
2026-01-16 added wopr to all workzones
2026-01-16 Add files via upload
    added factory default option
2026-01-16 added factory default option
2026-01-20 updated code for half timezones
2026-01-20 Updated NTP settings for timezones
2026-01-20 made rack image a little smaller
2026-01-22 Rename 2026-01-03 07_11_50-.png to 19inch-1.png
2026-01-22 Rename 2026-01-03 07_11_12-.png to 19inch-2.png
2026-01-22 Rename 2026-01-03 07_11_31-.png to 19inch-3.png
2026-01-22 added 10inch version
